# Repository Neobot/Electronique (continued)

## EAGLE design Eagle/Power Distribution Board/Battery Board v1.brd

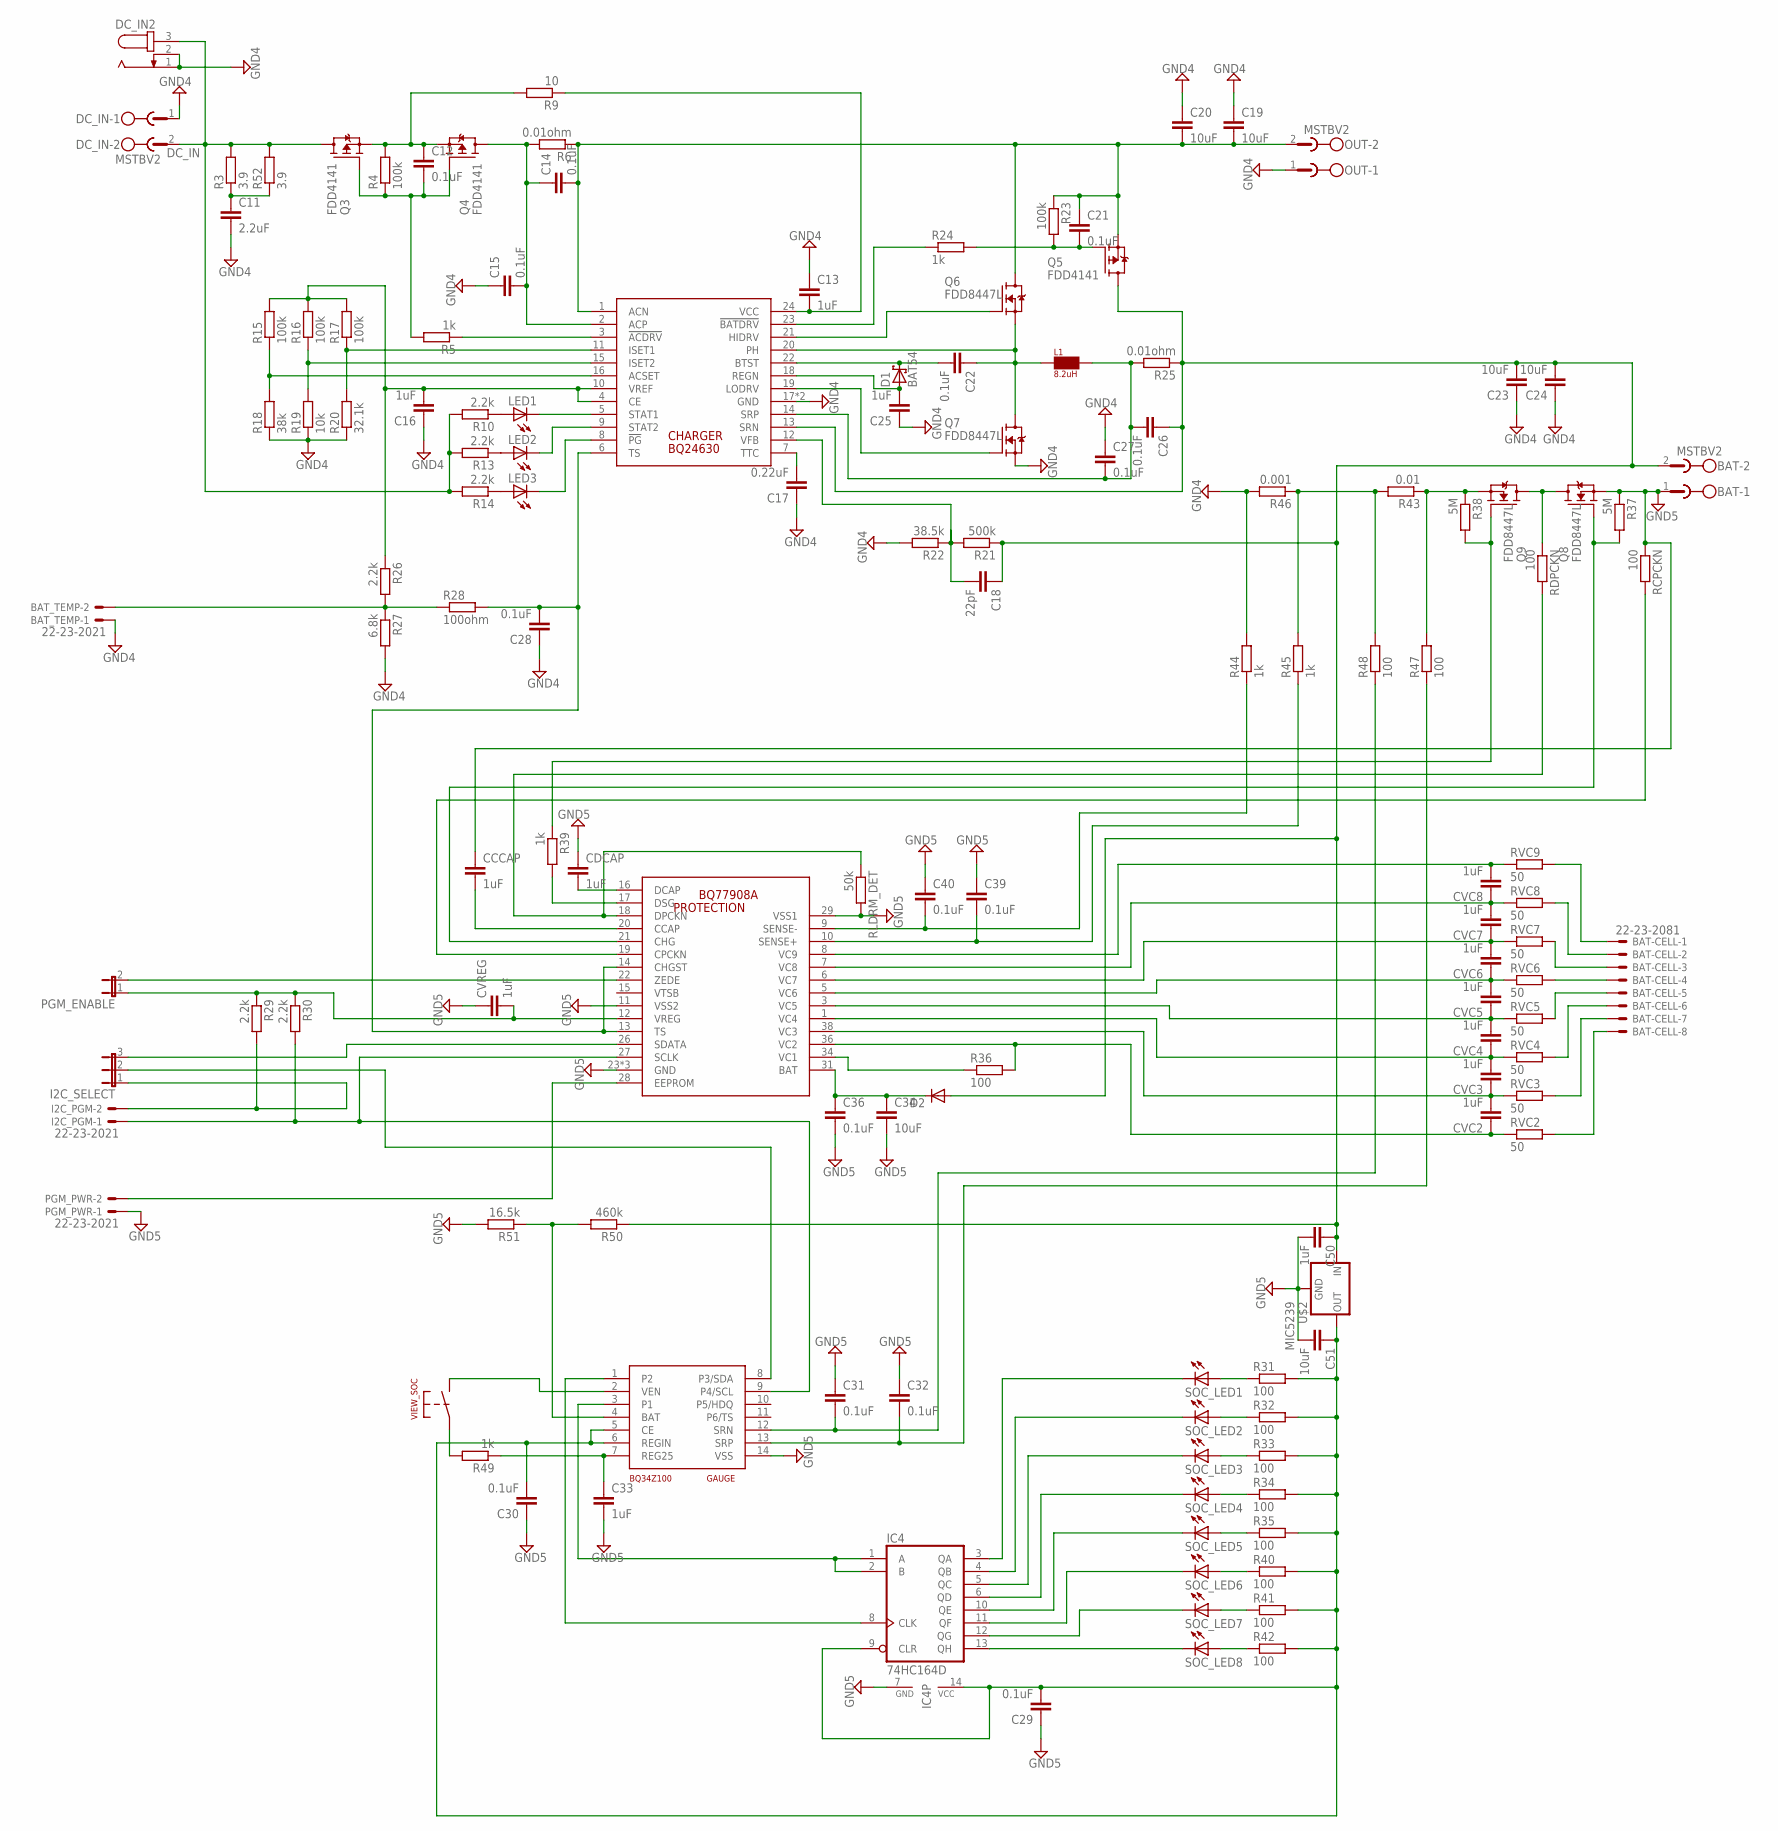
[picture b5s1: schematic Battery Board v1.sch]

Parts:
BAT: MSTBV2; MPN MSTBV 2,5/2-GF-5.08
BAT-CELL: 22-23-2081
BAT_TEMP: 22-23-2021; MPN 22-23-2021
C11: 2.2uF; C1206
C12, C14, C15, C21, C22, C26, C27, C28, C29, C30, C31, C32, C39, C40: 0.1uF; C0603
C13: 1uF; C1206
C16, C25: 1uF; C0805
C17: 0.22uF; C0603
C18: 22pF; C0603
C19, C20, C23, C24: 10uF; C1812
C33, C50: 1uF; C0603
C34: 10uF; C1210
C36: 0.1uF; C1210
C51: 10uF; C0603
CCCAP: 1uF; C1206
CDCAP: 1uF; C1206
CHARGER: BQ24630; QFN-24
CVC2, CVC3, CVC4, CVC5, CVC6, CVC7, CVC8: 1uF; C0603
CVREG: 1uF; C0603
D1: BAT54; SOT23
D2: DIODE-SOD123; SOD123
DC_IN: MSTBV2
DC_IN2: JACK-PLUG1; SPC4078
GAUGE: BQ34Z100; TSSOP-14-0.65MM
I2C_PGM: 22-23-2021; MPN 22-23-2021
I2C_SELECT: JP2E; JP2
IC4: 74HC164D; SO14
L1: 8.2uH; 5050CE
LED1, LED2, LED3: LEDCHIP-LED0603; CHIP-LED0603
OUT: MSTBV2; MPN MSTBV 2,5/2-GF-5.08
PGM_ENABLE: JP1E; JP1
PGM_PWR: 22-23-2021; MPN 22-23-2021
PROTECTION: BQ77908A; TSSOP-38-0.5MM
Q3, Q4, Q5: FDD4141; TO252
Q6, Q7, Q8, Q9: FDD8447L; TO252
R3, R52: 3.9; R1206
R4, R23: 100k; R0603
R5, R24, R39, R44, R45, R49: 1k; R0603
R6, R25: 0.01ohm; R2010
R9: 10; R1206
R10, R13, R14, R26, R29, R30: 2.2k; R0603
R15, R16, R17: 100k; R0805
R18: 38k; R0805
R19: 10k; R0805
R20: 32.1k; R0805
R21: 500k; R0805
R22: 38.5k; R0805
R27: 6.8k; R0603
R28: 100ohm; R0603
R31, R32, R33, R34, R35, R36, R40, R41, R42, R47, R48: 100; R0603
R37, R38: 5M; R0603
R43: 0.01; R2010
R46: 0.001; R2010
R50: 460k; R0805
R51: 16.5k; R0603
RCPCKN: 100; R0603
RDPCKN: 100; R0603
RLDRM_DET: 50k; R0603
RVC2, RVC3, RVC4, RVC5, RVC6, RVC7, RVC8, RVC9: 50; R1206
SOC_LED1, SOC_LED2, SOC_LED3, SOC_LED4, SOC_LED5, SOC_LED6, SOC_LED7, SOC_LED8: LEDCHIP-LED0603; CHIP-LED0603
U$2: MIC5239; SOT223
VIEW_SOC: PUSHBUTTON

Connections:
DC_IN: DC_IN.2, DC_IN2.3, Q3.3 (D), R3.2, R10.2, R13.2, R14.2, R52.2
GND4: BAT_TEMP.1, C11.2, C13.1, C15.1, C16.1, C17.1, C19.1, C20.1, C23.1, C24.1, C25.1, C27.1, C28.1, CHARGER.17 (GND), CHARGER.THERMAL (GND), DC_IN.1, DC_IN2.1, DC_IN2.2, OUT.1, Q7.2 (S), R18.1, R19.1, R20.1, R22.2, R27.2, R44.2, R46.2
GND5: BAT.1, C29.1, C30.1, C31.1, C32.1, C33.2, C34.2, C36.2, C39.1, C40.1, C50.2, C51.2, CCCAP.1, CDCAP.1, CVREG.1, GAUGE.14 (VSS), IC4.7 (GND), PGM_PWR.1, PROTECTION.11 (VSS2), PROTECTION.23 (GND), PROTECTION.24 (GND), PROTECTION.25 (GND), PROTECTION.29 (VSS1), Q8.2 (S), R37.1, R51.2, RCPCKN.1, RLDRM_DET.2, U$2.2 (GND), U$2.4 (GND)
unnamed: C11.1, R3.1, R52.1
unnamed: C12.1, Q3.2 (S), Q4.2 (S), R4.2, R9.2
unnamed: C12.2, Q3.1 (G), Q4.1 (G), R4.1, R5.2
unnamed: CHARGER.3 (!ACDRV!), R5.1
unnamed: C17.2, CHARGER.7 (TTC)
unnamed: C13.2, CHARGER.24 (VCC), R9.1
unnamed: C14.2, C19.2, C20.2, C21.1, CHARGER.1 (ACN), OUT.2, Q5.2 (S), Q6.3 (D), R6.1, R23.1
unnamed: C18.2, CHARGER.12 (VFB), R21.2, R22.1
unnamed: CHARGER.5 (STAT1), LED1.C
unnamed: CHARGER.9 (STAT2), LED2.C
unnamed: CHARGER.8 (!PG!), LED3.C
unnamed: LED1.A, R10.1
unnamed: LED2.A, R13.1
unnamed: LED3.A, R14.1
unnamed: BAT_TEMP.2, R26.2, R27.1, R28.1
unnamed: CHARGER.16 (ACSET), R15.1, R18.2
unnamed: CHARGER.15 (ISET2), R16.1, R19.2
unnamed: CHARGER.11 (ISET1), R17.1, R20.2
unnamed: Q8.3 (D), Q9.3 (D), RDPCKN.1
unnamed: C28.2, CHARGER.6 (TS), PROTECTION.13 (TS), PROTECTION.14 (CHGST), R28.2
unnamed: C21.2, Q5.1 (G), R23.2, R24.2
unnamed: C32.2, GAUGE.13 (SRP), R47.1
unnamed: CHARGER.23 (!BATDRV!), R24.1
unnamed: CHARGER.21 (HIDRV), Q6.1 (G)
unnamed: C22.1, CHARGER.20 (PH), L1.P$1, Q6.2 (S), Q7.3 (D)
unnamed: C22.2, CHARGER.22 (BTST), D1.3 (C)
unnamed: C34.1, C36.1, D2.C, PROTECTION.31 (BAT)
unnamed: C26.2, C27.2, CHARGER.14 (SRP), L1.P$2, R25.2
unnamed: BAT-CELL.8, RVC2.2
unnamed: C25.2, CHARGER.18 (REGN), D1.1 (A)
unnamed: CHARGER.19 (LODRV), Q7.1 (G)
unnamed: CVC8.2, PROTECTION.8 (VC9), RVC9.1
unnamed: CVC2.1, PROTECTION.36 (VC2), R36.2, RVC2.1
unnamed: CVC4.2, CVC5.1, PROTECTION.3 (VC5), RVC5.1
unnamed: CVC2.2, CVC3.1, PROTECTION.38 (VC3), RVC3.1
unnamed: PROTECTION.34 (VC1), R36.1
unnamed: CVC6.2, CVC7.1, PROTECTION.6 (VC7), RVC7.1
unnamed: CVC5.2, CVC6.1, PROTECTION.5 (VC6), RVC6.1
unnamed: CVC3.2, CVC4.1, PROTECTION.1 (VC4), RVC4.1
unnamed: BAT-CELL.7, RVC3.2
unnamed: BAT-CELL.6, RVC4.2
unnamed: BAT-CELL.5, RVC5.2
unnamed: BAT-CELL.4, RVC6.2
unnamed: BAT-CELL.3, RVC7.2
unnamed: BAT-CELL.2, RVC8.2
unnamed: BAT-CELL.1, RVC9.2
unnamed: C33.1, GAUGE.7 (REG25), R49.1
unnamed: Q9.1 (G), R38.2, R39.1
unnamed: PROTECTION.21 (CHG), Q8.1 (G), R37.2
unnamed: PROTECTION.17 (DSG), R39.2
unnamed: CDCAP.2, PROTECTION.16 (DCAP)
unnamed: CVC7.2, CVC8.1, PROTECTION.7 (VC8), RVC8.1
unnamed: PROTECTION.18 (DPCKN), RDPCKN.2, RLDRM_DET.1
unnamed: R31.1, SOC_LED1.A
unnamed: PROTECTION.19 (CPCKN), RCPCKN.2
unnamed: CCCAP.2, PROTECTION.20 (CCAP)
unnamed: R32.1, SOC_LED2.A
unnamed: C39.2, PROTECTION.10 (SENSE+), R45.1
unnamed: C40.2, PROTECTION.9 (SENSE-), R44.1
unnamed: GAUGE.9 (P4/SCL), I2C_PGM.1, PROTECTION.27 (SCLK), R30.2
unnamed: I2C_PGM.2, I2C_SELECT.1, R29.2
unnamed: R33.1, SOC_LED3.A
unnamed: PGM_ENABLE.2, PROTECTION.22 (ZEDE)
unnamed: PGM_PWR.2, PROTECTION.28 (EEPROM)
unnamed: C29.2, C30.2, C51.1, GAUGE.5 (CE), GAUGE.6 (REGIN), IC4.9 (CLR), IC4.14 (VCC), R31.2, R32.2, R33.2, R34.2, R35.2, R40.2, R41.2, R42.2, U$2.3 (OUT)
unnamed: R34.1, SOC_LED4.A
unnamed: R35.1, SOC_LED5.A
unnamed: R40.1, SOC_LED6.A
unnamed: R41.1, SOC_LED7.A
unnamed: R42.1, SOC_LED8.A
unnamed: IC4.13 (QH), SOC_LED8.C
unnamed: IC4.3 (QA), SOC_LED1.C
unnamed: IC4.4 (QB), SOC_LED2.C
unnamed: IC4.5 (QC), SOC_LED3.C
unnamed: IC4.6 (QD), SOC_LED4.C
unnamed: IC4.10 (QE), SOC_LED5.C
unnamed: IC4.12 (QG), SOC_LED7.C
unnamed: I2C_SELECT.3, PROTECTION.26 (SDATA)
unnamed: GAUGE.8 (P3/SDA), I2C_SELECT.2
unnamed: C31.2, GAUGE.12 (SRN), R48.1
unnamed: GAUGE.3 (P1), IC4.1 (A), IC4.2 (B)
unnamed: GAUGE.1 (P2), IC4.8 (CLK)
unnamed: R49.2, VIEW_SOC.P$1, VIEW_SOC.P$2
unnamed: GAUGE.2 (VEN), VIEW_SOC.P$3, VIEW_SOC.P$4
unnamed: GAUGE.4 (BAT), R50.2, R51.1
unnamed: BAT.2, C18.1, C23.2, C24.2, C26.1, C50.1, CHARGER.13 (SRN), D2.A, Q5.3 (D), R21.1, R25.1, R50.1, U$2.1 (IN)
unnamed: CVREG.2, PGM_ENABLE.1, PROTECTION.12 (VREG), R29.1, R30.1
unnamed: R43.2, R45.2, R46.1, R48.2
unnamed: Q9.2 (S), R38.1, R43.1, R47.2
SI7617DN: C14.1, C15.2, CHARGER.2 (ACP), Q4.3 (D), R6.2
SOC_LED6: IC4.11 (QF), SOC_LED6.C
VREF: C16.2, CHARGER.4 (CE), CHARGER.10 (VREF), R15.2, R16.2, R17.2, R26.1

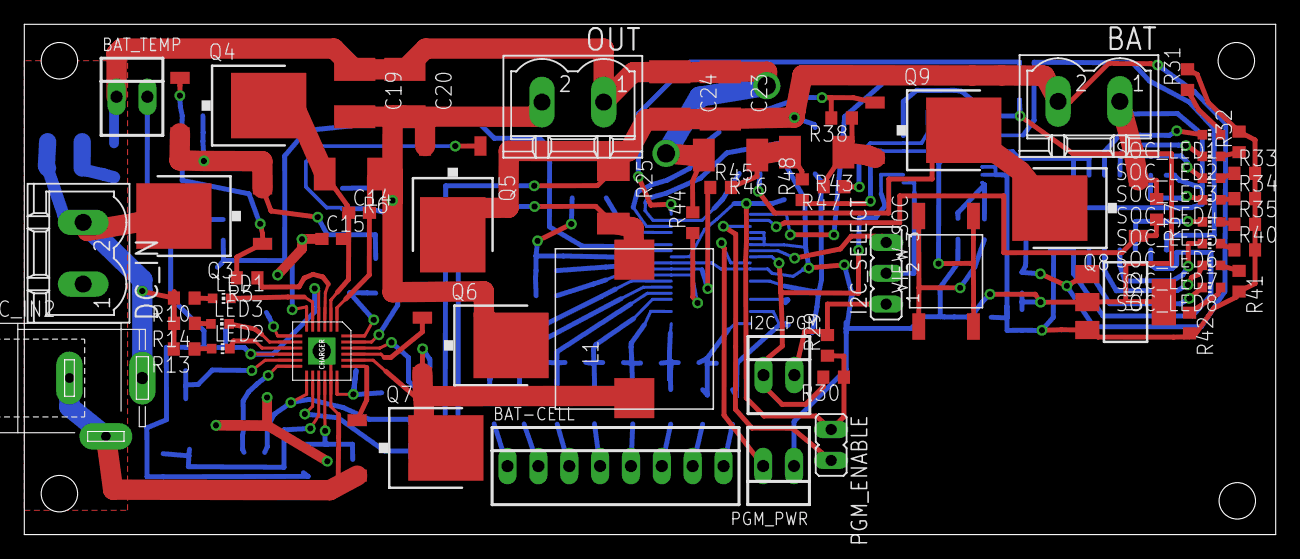
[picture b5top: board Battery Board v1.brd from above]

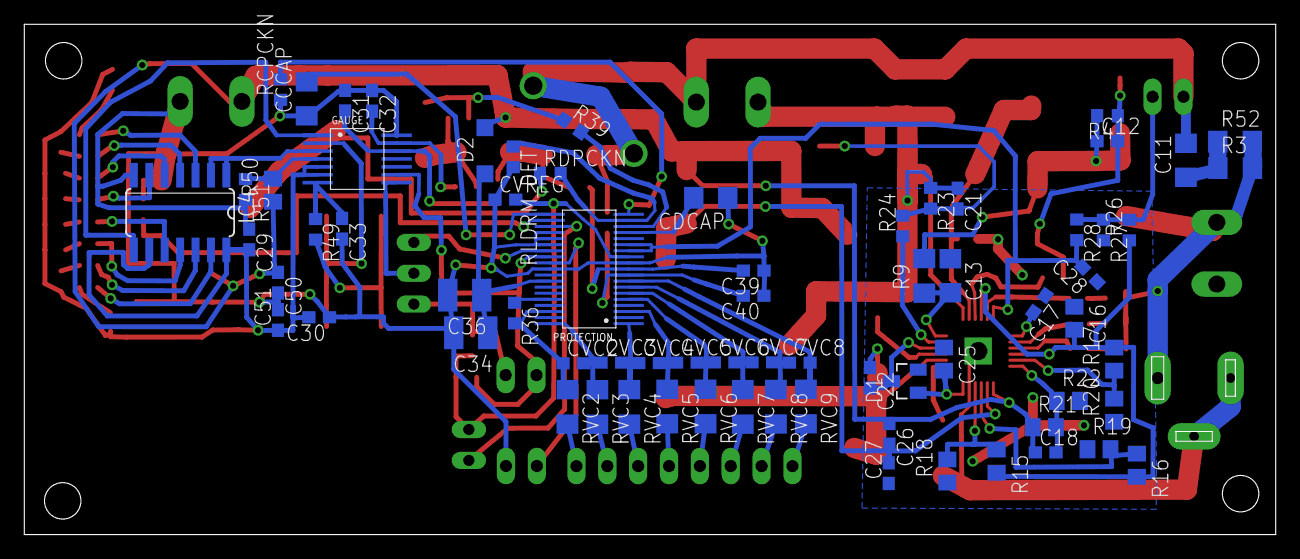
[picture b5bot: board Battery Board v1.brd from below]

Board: 2 copper layers, 103.0 x 42.0 mm, 133 parts (71 on the bottom side), 95 nets.

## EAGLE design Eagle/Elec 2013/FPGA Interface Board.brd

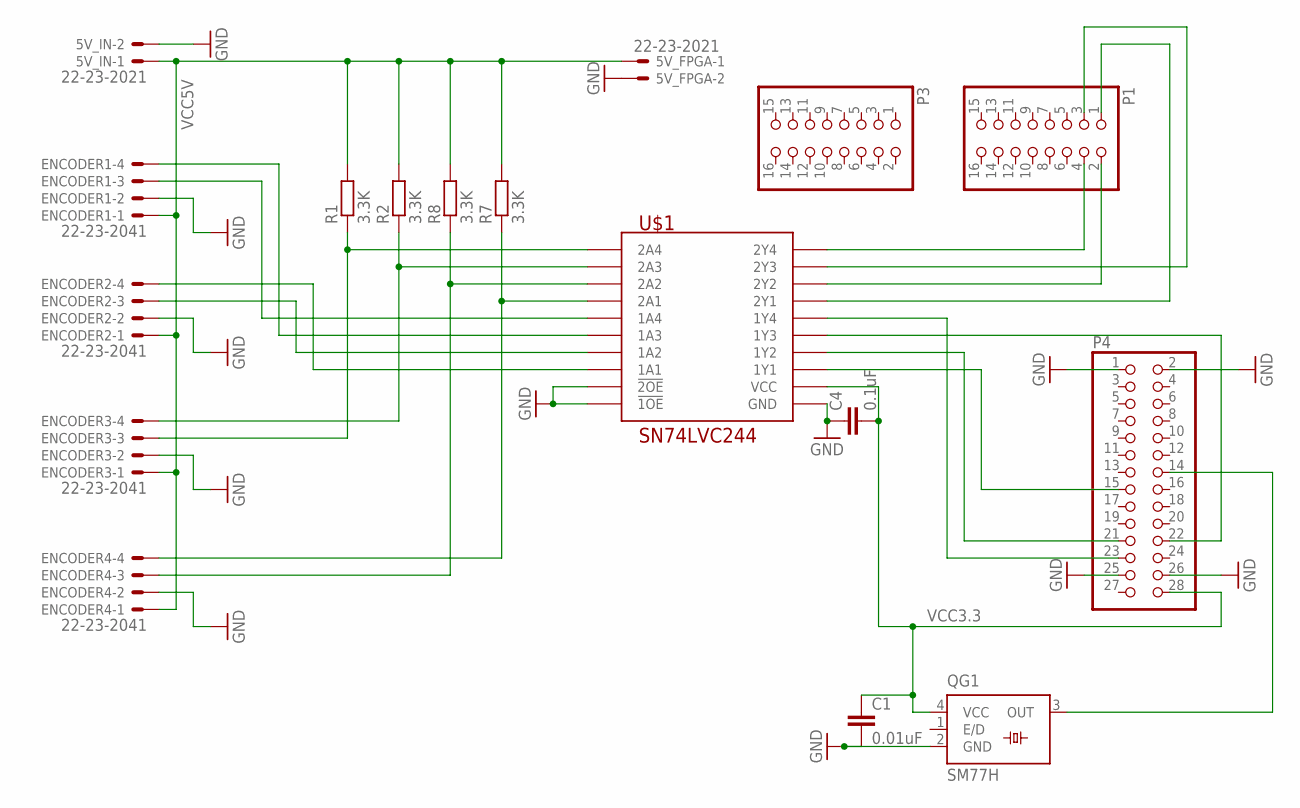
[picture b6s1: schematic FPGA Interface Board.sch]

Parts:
5V_FPGA: 22-23-2021; MPN 22-23-2021
5V_IN: 22-23-2021
C1: 0.01uF; C0603
C4: 0.1uF; C0603
ENCODER1, ENCODER2, ENCODER3, ENCODER4: 22-23-2041
P1, P3: PINHD-2X8; 2X08
P4: PINHD-2X14; 2X14
QG1: SM77H
R1, R2, R7, R8: 3.3K; R0603
U$1: SN74LVC244; TSSOP-20-0.65MM

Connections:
GND: 5V_FPGA.2, 5V_IN.2, C1.2, C4.1, ENCODER1.2, ENCODER2.2, ENCODER3.2, ENCODER4.2, P4.1, P4.2, P4.25, P4.26, QG1.2 (GND), U$1.P$1 (!1OE), U$1.P$10 (GND), U$1.P$19 (!2OE)
unnamed: P4.14, QG1.3 (OUT)
unnamed: P4.23, U$1.P$12 (1Y4)
unnamed: P4.21, U$1.P$16 (1Y2)
unnamed: P4.15, U$1.P$18 (1Y1)
unnamed: P4.22, U$1.P$14 (1Y3)
unnamed: P1.4, U$1.P$3 (2Y4)
unnamed: P1.2, U$1.P$7 (2Y2)
unnamed: P1.1, U$1.P$9 (2Y1)
unnamed: P1.3, U$1.P$5 (2Y3)
unnamed: ENCODER3.3, R1.1, U$1.P$17 (2A4)
unnamed: ENCODER3.4, R2.1, U$1.P$15 (2A3)
unnamed: ENCODER4.3, R8.1, U$1.P$13 (2A2)
unnamed: ENCODER4.4, R7.1, U$1.P$11 (2A1)
unnamed: ENCODER1.3, U$1.P$8 (1A4)
unnamed: ENCODER1.4, U$1.P$6 (1A3)
unnamed: ENCODER2.3, U$1.P$4 (1A2)
unnamed: ENCODER2.4, U$1.P$2 (1A1)
VCC3.3: C1.1, C4.2, P4.28, QG1.4 (VCC), U$1.P$20 (VCC)
VCC5V: 5V_FPGA.1, 5V_IN.1, ENCODER1.1, ENCODER2.1, ENCODER3.1, ENCODER4.1, R1.2, R2.2, R7.2, R8.2

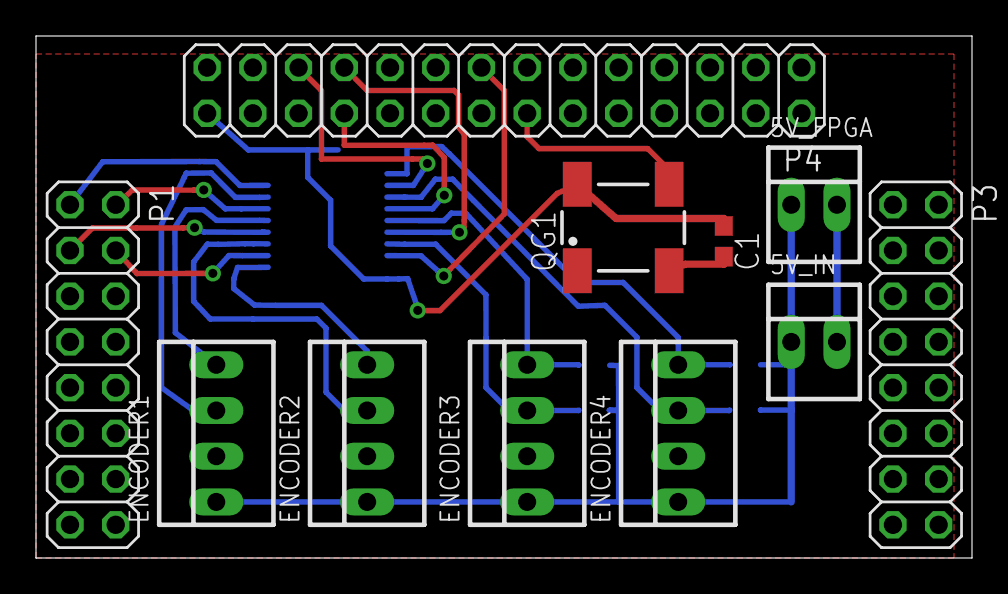
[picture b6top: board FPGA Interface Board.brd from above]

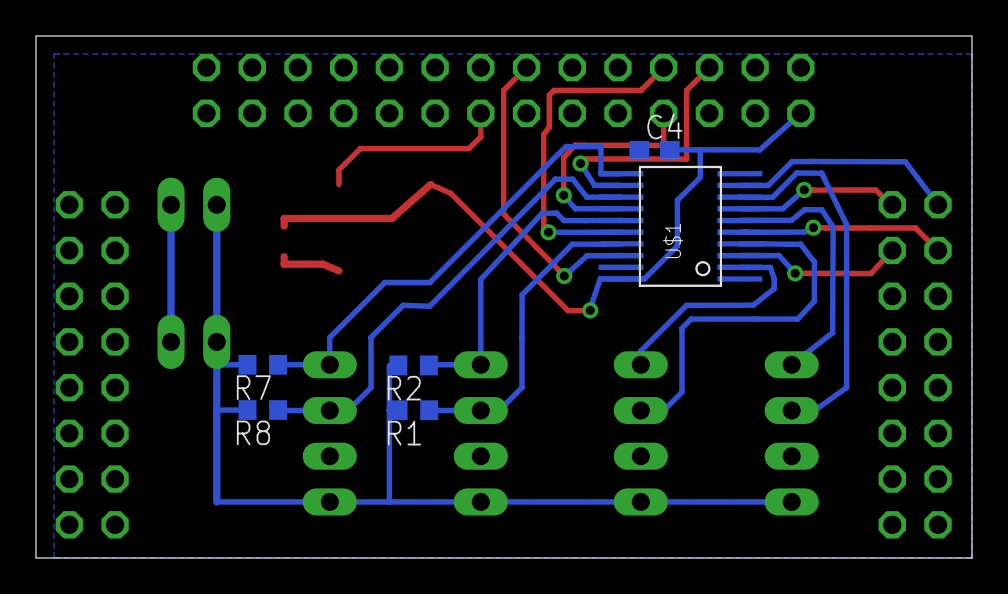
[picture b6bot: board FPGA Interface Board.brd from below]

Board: 2 copper layers, 52.0 x 29.0 mm, 17 parts (6 on the bottom side), 20 nets.

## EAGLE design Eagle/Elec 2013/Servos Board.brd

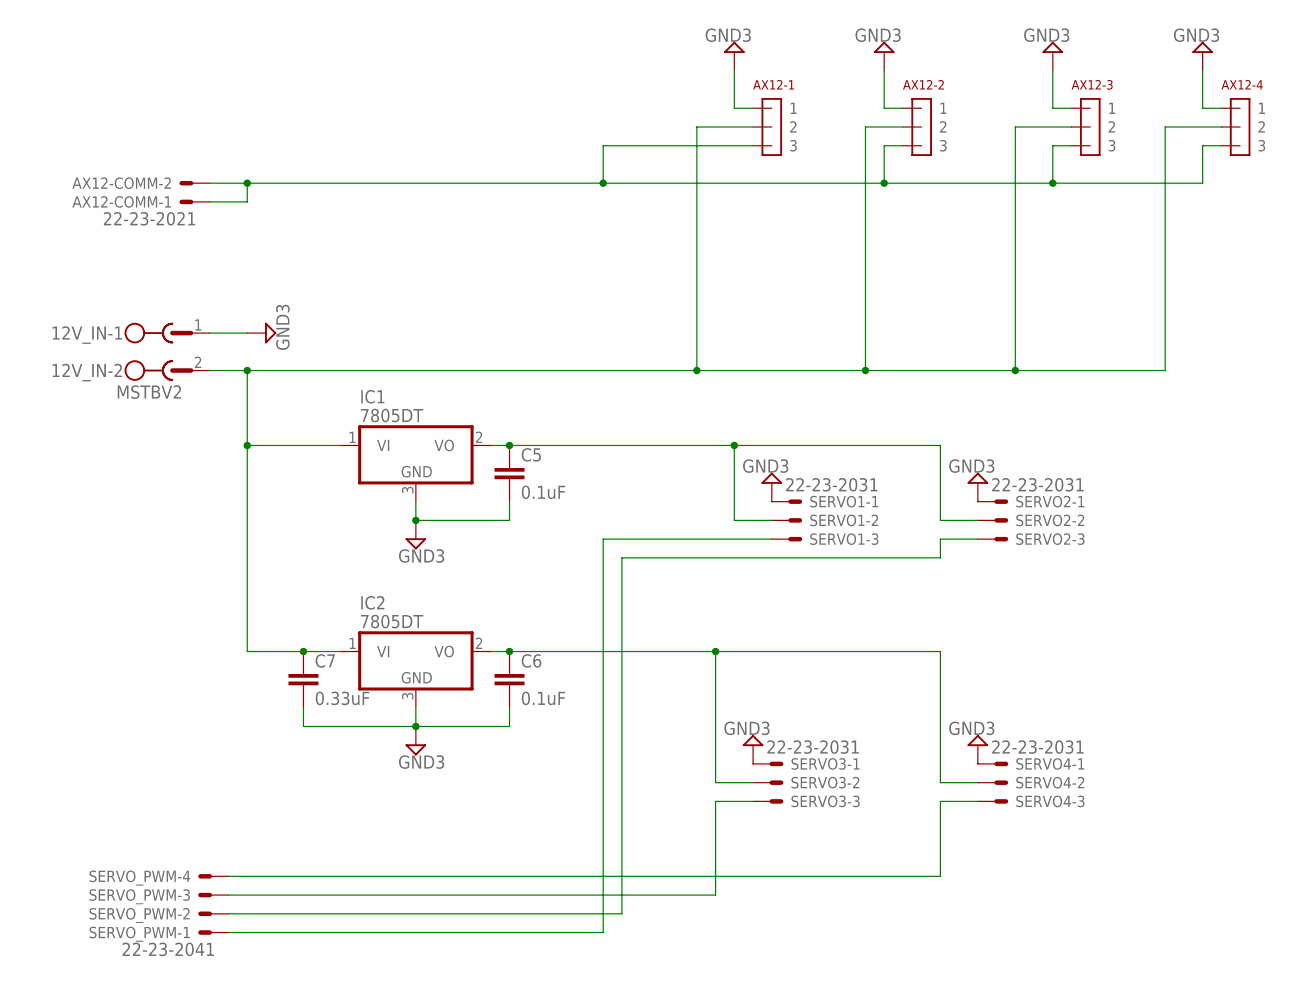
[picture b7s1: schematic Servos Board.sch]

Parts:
12V_IN: MSTBV2
AX12-1, AX12-2, AX12-3, AX12-4: 22-03-5035
AX12-COMM: 22-23-2021
C5, C6: 0.1uF; C0603
C7: 0.33uF; C0603
IC1, IC2: 7805DT; TO252
SERVO1, SERVO2, SERVO3, SERVO4: 22-23-2031
SERVO_PWM: 22-23-2041

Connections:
GND3: 12V_IN.1, AX12-1.P$1 (1), AX12-2.P$1 (1), AX12-3.P$1 (1), AX12-4.P$1 (1), C5.2, C6.2, C7.2, IC1.3 (GND), IC2.3 (GND), SERVO1.1, SERVO2.1, SERVO3.1, SERVO4.1
unnamed: SERVO1.3, SERVO_PWM.1
unnamed: SERVO2.3, SERVO_PWM.2
unnamed: SERVO3.3, SERVO_PWM.3
unnamed: C6.1, IC2.2 (VO), SERVO3.2, SERVO4.2
unnamed: SERVO4.3, SERVO_PWM.4
unnamed: 12V_IN.2, AX12-1.P$2 (2), AX12-2.P$2 (2), AX12-3.P$2 (2), AX12-4.P$2 (2), C7.1, IC1.1 (VI), IC2.1 (VI)
unnamed: C5.1, IC1.2 (VO), SERVO1.2, SERVO2.2
unnamed: AX12-1.P$3 (3), AX12-2.P$3 (3), AX12-3.P$3 (3), AX12-4.P$3 (3), AX12-COMM.1, AX12-COMM.2

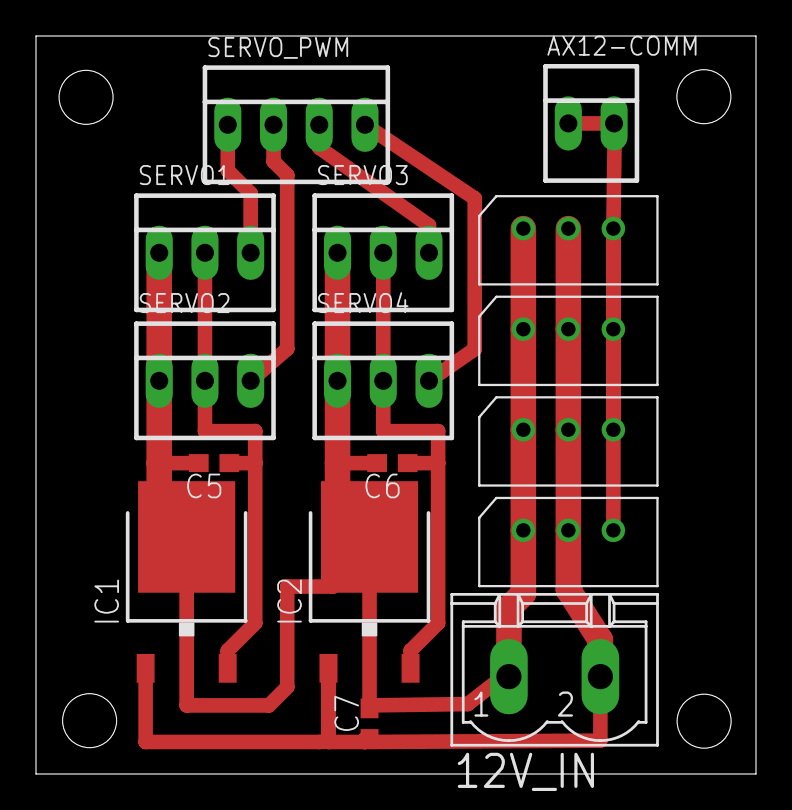
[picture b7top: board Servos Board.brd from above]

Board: 2 copper layers, 40.0 x 41.0 mm, 16 parts (0 on the bottom side), 9 nets.

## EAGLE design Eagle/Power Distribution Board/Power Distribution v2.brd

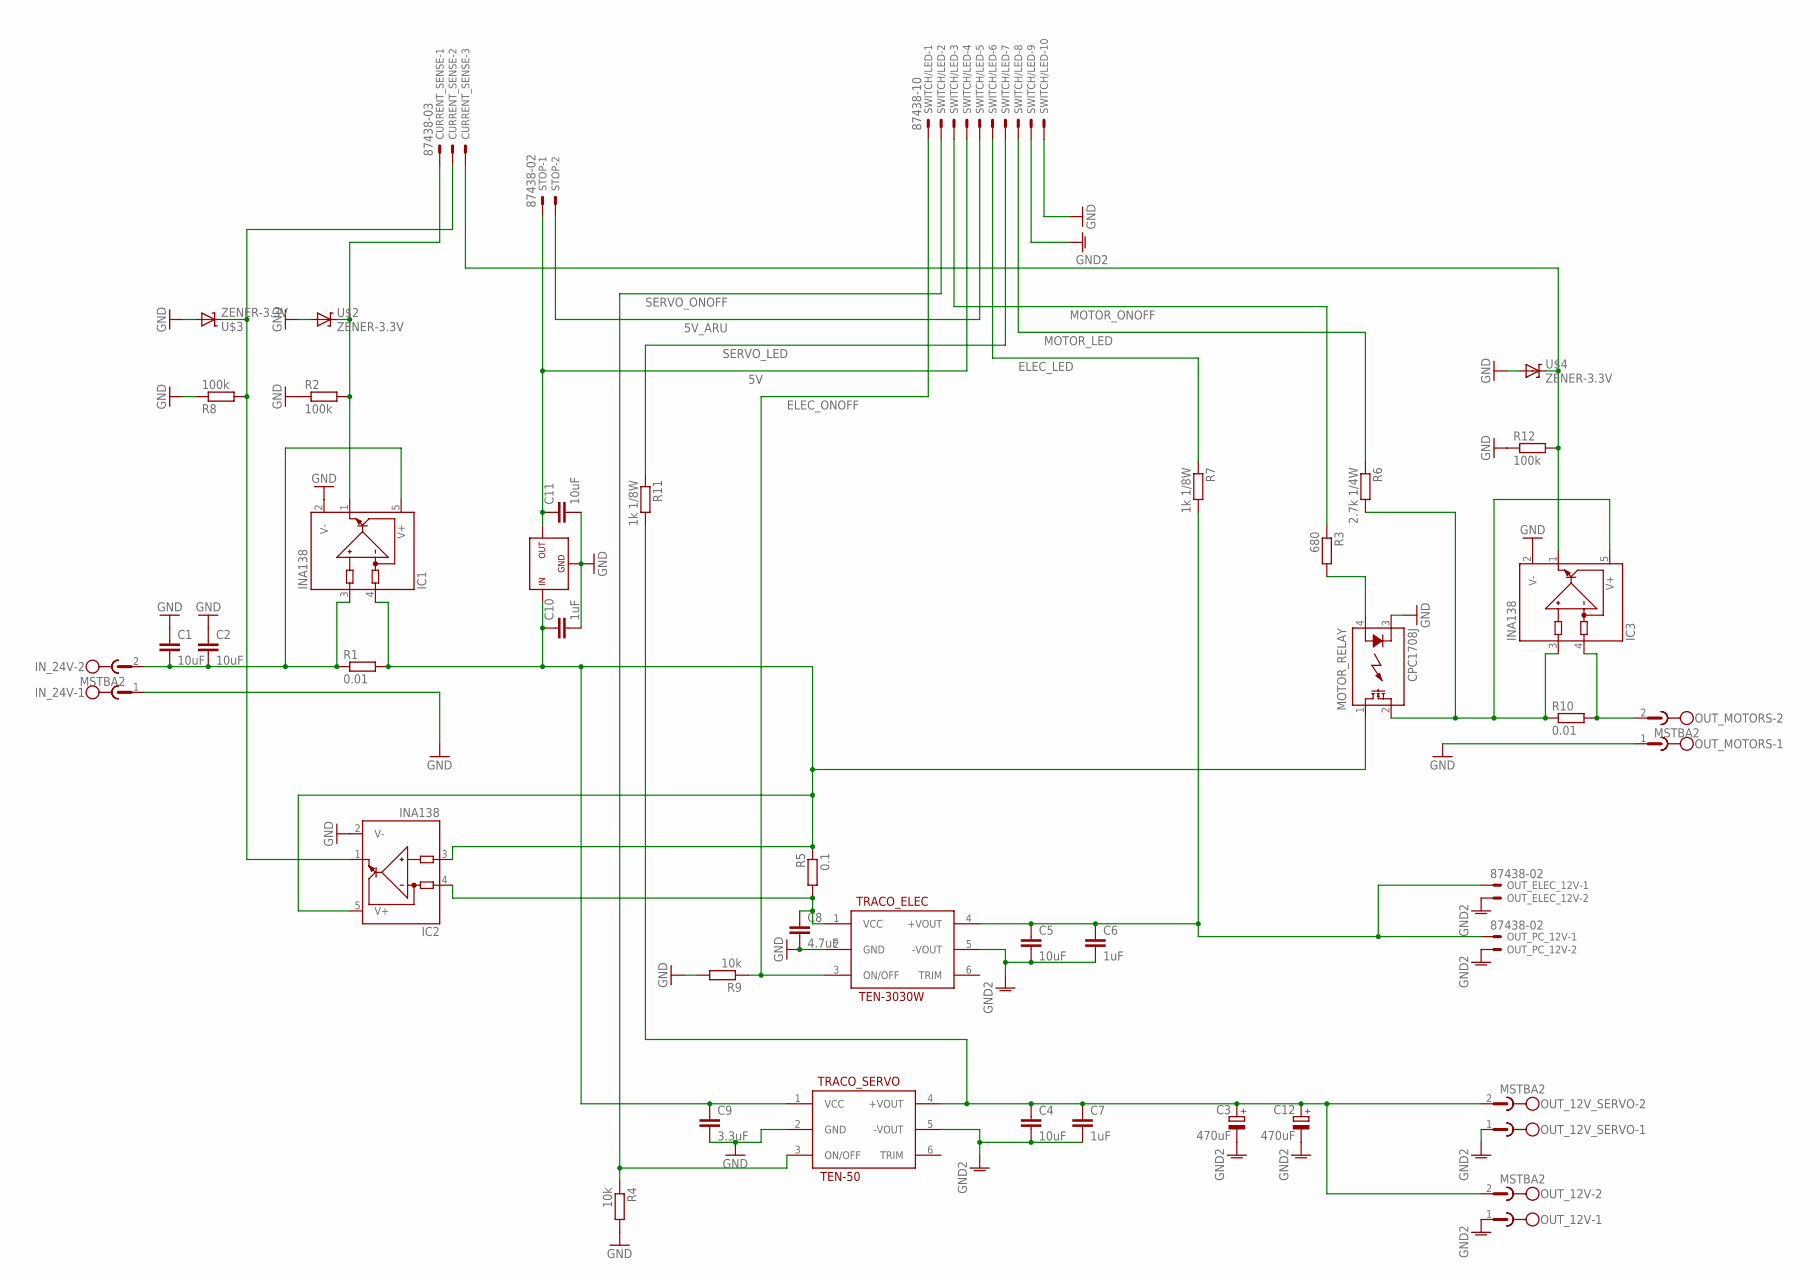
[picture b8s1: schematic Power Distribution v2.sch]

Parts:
C1, C2, C4, C5: 10uF; C1812
C3, C12: 470uF; E5-10,5
C6, C7, C10: 1uF; C0805
C8: 4.7uF; C1210
C9: 3.3uF; C1210
C11: 10uF; C0805
CURRENT_SENSE: 87438-03
IC1, IC2, IC3: INA138; SOT23-5
IN_24V: MSTBA2
MOTOR_RELAY: CPC1708J; I4-PAC
OUT_12V, OUT_12V_SERVO: MSTBA2
OUT_ELEC_12V: 87438-02
OUT_MOTORS: MSTBA2
OUT_PC_12V: 87438-02
R1, R10: 0.01; R2010
R2, R8, R12: 100k; R0603
R3: 680; R0603
R4, R9: 10k; R0603
R5: 0.1; R2010
R6: 2.7k 1/4W; R1206
R7, R11: 1k 1/8W; R0603
STOP: 87438-02
SWITCH/LED: 87438-10
TRACO_ELEC: TEN-3030W; TRACO2X1
TRACO_SERVO: TEN-50; TRACO2X1_50W
U$1: MIC5239; SOT-223
U$2, U$3, U$4: ZENER-3.3V; SOD-323

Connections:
5V: C11.1, STOP.1, SWITCH/LED.4, U$1.3 (OUT)
5V_ARU: STOP.2, SWITCH/LED.5
12V_ELEC: C5.1, C6.1, OUT_ELEC_12V.1, OUT_PC_12V.1, R7.2, TRACO_ELEC.4 (+VOUT)
12V_MOTORS: IC3.3 (IN+), IC3.5 (V+), MOTOR_RELAY.2 (DS2), R6.2, R10.1
12V_SERVO: C3.+, C4.1, C7.1, C12.+, OUT_12V.2, OUT_12V_SERVO.2, R11.2, TRACO_SERVO.4 (+VOUT)
24VIN: C9.1, C10.1, IC1.4 (IN-), IC2.3 (IN+), IC2.5 (V+), MOTOR_RELAY.1 (DS1), R1.2, R5.1, TRACO_SERVO.1 (VCC), U$1.1 (IN)
AGND: C3.-, C4.2, C5.2, C6.2, C7.2, C12.-, OUT_12V.1, OUT_12V_SERVO.1, OUT_ELEC_12V.2, OUT_PC_12V.2, SWITCH/LED.9, TRACO_ELEC.5 (-VOUT), TRACO_SERVO.5 (-VOUT)
ELEC_CURRENT: CURRENT_SENSE.2, IC2.1 (OUT), R8.2, U$3.1 (C)
ELEC_LED: R7.1, SWITCH/LED.6
ELEC_ONOFF: R9.1, SWITCH/LED.1, TRACO_ELEC.3 (ON/OFF)
GND: C1.1, C2.1, C8.2, C9.2, C10.2, C11.2, IC1.2 (V-), IC2.2 (V-), IC3.2 (V-), IN_24V.1, MOTOR_RELAY.3 (K), OUT_MOTORS.1, R2.1, R4.2, R8.1, R9.2, R12.1, SWITCH/LED.10, TRACO_ELEC.2 (GND), TRACO_SERVO.2 (GND), U$1.2 (GND), U$1.4 (GND), U$2.2 (A), U$3.2 (A), U$4.2 (A)
IN_CURRENT: CURRENT_SENSE.1, IC1.1 (OUT), R2.2, U$2.1 (C)
MOTORS_CURRENT: CURRENT_SENSE.3, IC3.1 (OUT), R12.2, U$4.1 (C)
MOTOR_LED: R6.1, SWITCH/LED.8
MOTOR_ONOFF: R3.1, SWITCH/LED.3
unnamed: IC3.4 (IN-), OUT_MOTORS.2, R10.2
unnamed: C1.2, C2.2, IC1.3 (IN+), IC1.5 (V+), IN_24V.2, R1.1
unnamed: C8.1, IC2.4 (IN-), R5.2, TRACO_ELEC.1 (VCC)
unnamed: MOTOR_RELAY.4 (A), R3.2
SERVO_LED: R11.1, SWITCH/LED.7
SERVO_ONOFF: R4.1, SWITCH/LED.2, TRACO_SERVO.3 (ON/OFF)

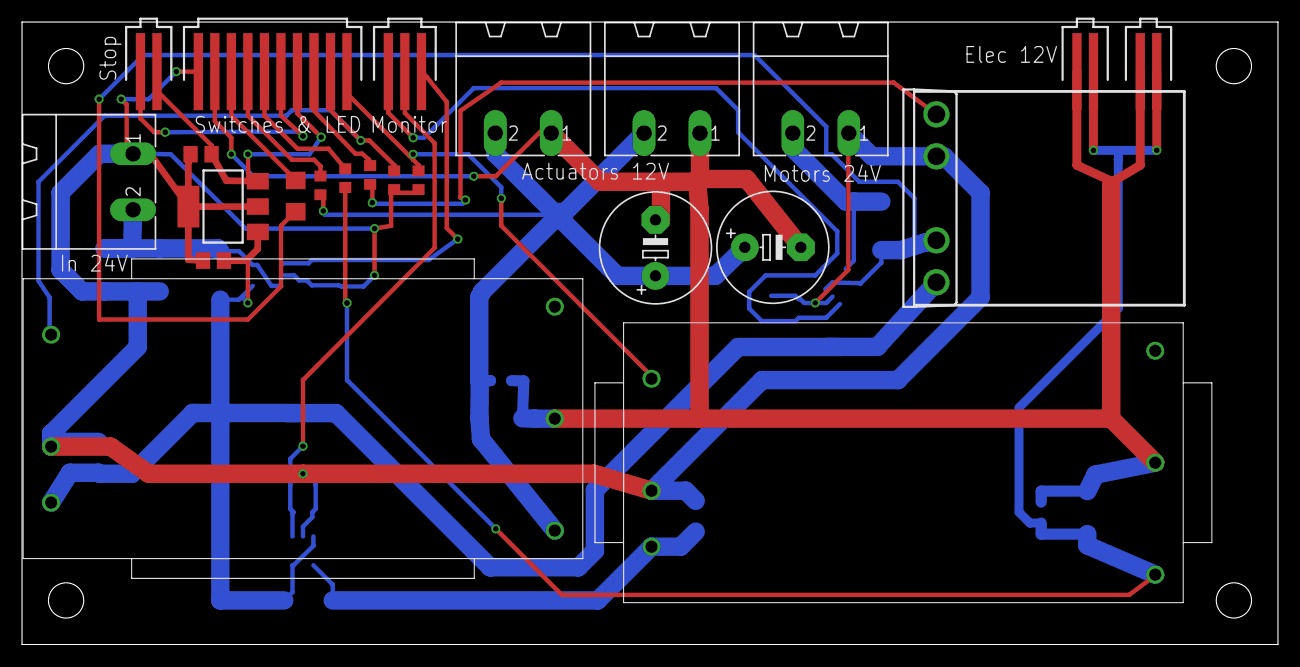
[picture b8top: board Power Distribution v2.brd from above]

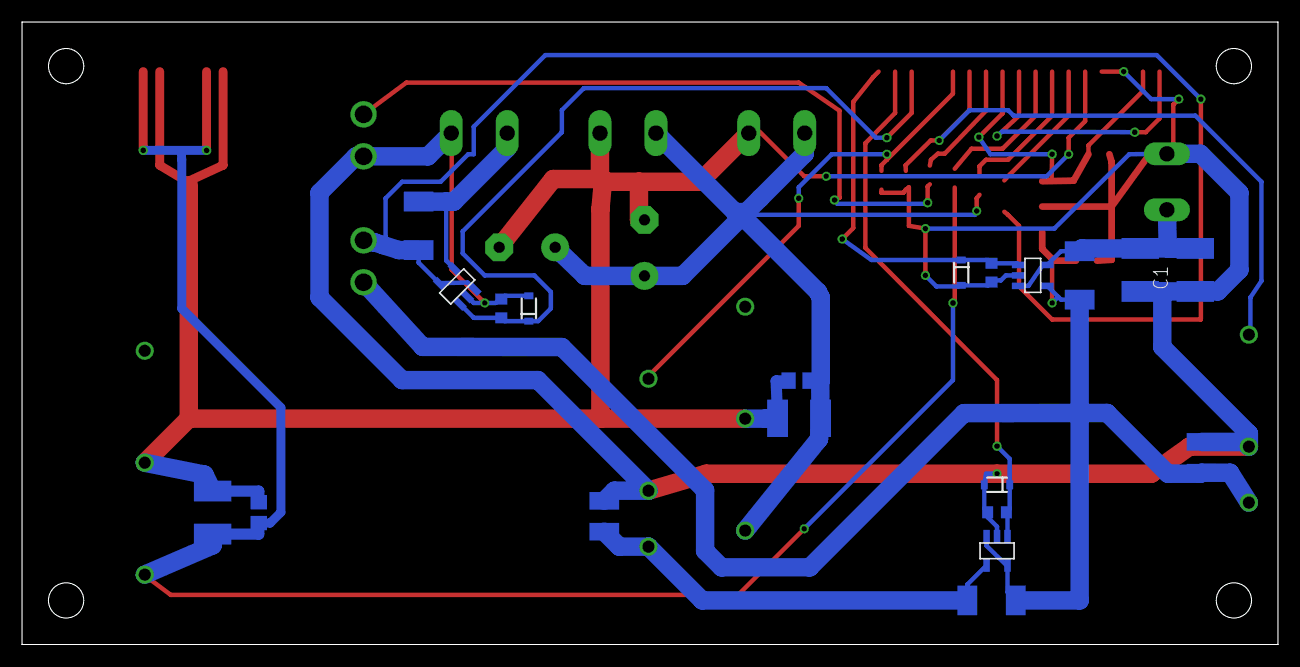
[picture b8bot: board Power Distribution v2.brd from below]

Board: 2 copper layers, 114.0 x 56.5 mm, 43 parts (20 on the bottom side), 21 nets.

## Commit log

2013-11-16 transfer from svn
2014-02-03 Reorganise projects & cleanup
2014-02-03 New servo & aux motor board, updated Arduino shield, new battery board 2014
2014-03-12 Small fixes after testing cards
